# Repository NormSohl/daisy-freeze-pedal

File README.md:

# Daisy Freeze Pedal

A line-level freeze/drone floor pedal (mono in, stereo out) built on the Electrosmith Daisy Seed3, designed for playing hands-free alongside a WARBL wind controller or analog synths. Hold a footswitch to record, release to loop; the loop plays back as a Clouds-style granular freeze with sub-octave, fifth and octave voices.

## Status

Ready to order. The DSP and controls are proven in a browser bench model. The carrier is a bare, all-through-hole board you solder yourself, routed and DRC-clean; the case is a parametric OpenSCAD model. Next: order bare boards and parts, print the case, then port the bench engine to DaisySP.

## Panel

| Control | Type | Function |
|---|---|---|
| Freeze | Soft-touch momentary footswitch | Hold to record (up to 8 s), release to start looping |
| Clear | Soft-touch momentary footswitch | Tap: fade out the oldest layer. Hold 0.7 s: clear all |
| Dry | Pot | Passthrough level |
| Loop | Pot | Frozen 1:1 voice level |
| −8 | Pot | Sub-octave voice (1:2), 28 Hz high-pass |
| +5 | Pot | Fifth voice, 3:2 up or 3:4 down |
| +8 | Pot | Octave voice (2:1) |
| Fade | Pot | Layer swell-in and release time, 20 ms to 8 s |
| Texture | Pot | Macro: grain size, window shape and density, smooth → grainy |
| Single / Multi | Toggle | Single crossfades each capture over the last loop; Multi stacks up to 6 layers |
| +5 up / down | Toggle | Fifth above (3:2) or below (3:4) |
| LED | Bi-color | Red while recording, green while layers play, off when empty |

Fixed in firmware: grain spread, drift (random per-grain detune), output level. No reverb.

## I/O and power

- Three switched 1/4" jacks on the back face: In (mono), Out L/Mono, Out R.
  - The mono input feeds both codec inputs; the voices are spread across the stereo outputs.
  - Nothing in Out R: the firmware sums L+R to Out L (detected through Out R's ring switch).
- Line level in and out, no buffer and no input pad. The Seed3 clips at 3.6 Vpp (+4.3 dBu) and is rated to ±1.8 V, so keep very hot synth outputs turned down.
- The Seed3's own USB-C faces the back wall for 5 V power and firmware updates. Holding Clear at power-up will jump to the bootloader so the case never needs opening to flash.

## Hardware plan

- **One carrier PCB** mounted parallel to the panel carries everything except the footswitches:
  - Top side: seven 9 mm PCB-mount pots (plastic shafts), two PCB-mount mini toggles, LED on a spacer, and six resistors/capacitors.
  - Underside, rear edge: three right-angle 1/4" jacks with threaded bushings (nutted to the back wall so plug forces go into the case) and the Seed3 on female headers, its USB-C facing the back wall.
- **Footswitches** are nutted to the panel and wired to 2-pin locking connectors on the carrier; stomps never load solder joints.
- **Enclosure**: reinforced 3D-printed wedge, PETG or ASA. See [`enclosure/`](enclosure/).

## Parts

| Part | Choice | Notes |
|---|---|---|
| Pots (×7) | Alpha RV09AF-40-20K-B10K: 9 mm, vertical PCB mount, 20 mm knurled plastic shaft, B10K linear ([Jameco 2272207](https://www.jameco.com/z/RV09AF-40-20K-B10K-Taiwan-Alpha-9mm-Linear-Taper-Potentiometer-10K-Ohm-50mW-20-20mm-Long-Vertical-Knurled-Shaft_2272207.html), also Mouser and Tayda; the 25 mm length isn't stocked) | 7.6 mm tall body. Used bare, no knobs or caps: the knurled shaft is the grip, with a painted index line across its top face. |
| Toggles (×2) | E-Switch 100SP1T1B1M2RE (gold contacts; any 100SP1…M2 variant fits the board): SPDT on-on, PCB mount (M2), threaded 1/4"-40 bushing (B1, 8.89 mm) | Catalog p.2: single-pole body 8.89 mm; M2 drawing p.8: pins stand the body 1.5 mm off the board. Bushing base sits 10.39 mm above the PCB and seats on the panel underside; 6.4 mm of thread above the 2.5 mm panel takes the nut. The B4 variant's bushing is unthreaded. |
| Footswitches (×2) | Soft-touch momentary SPST, M12 bushing | Panel-mounted, wired to the carrier. |
| Jacks (×3) | Neutrik NMJ6HCD2: 1/4" stereo, switched, horizontal PCB, chrome ferrule with nut | Axis 7.53 mm from the PCB (drawing: 15.67 body, axis 8.14 below its top), 18.2 mm wide, 11.4 mm panel cut-out, panels under 4.7 mm. Mounted on the carrier underside. |
| Seed sockets | 2× 1×20 female headers, 2.54 mm, 8.5 mm tall | Seed3 hangs below the carrier on its 2.5 mm header spacer, USB-C to the back wall. |
| LED | 5 mm bi-colour red/green, common cathode, 3-lead, on a 4 mm LED spacer | Spacer puts the dome 0.3 mm below the panel top. Driven from two GPIOs through 470 Ω; pick R per die once the LED is chosen (a true-green die needs less). |
| Footswitch pads (×2) | J1/J2, 2 mm JST PH footprint, left unpopulated | Solder 24–26 AWG leads straight into the pads (polarity doesn't matter). A B2B-PH-K header and plug can be fitted later if you want the footswitches unpluggable. |
| Output coupling (×2 each) | 10 µF 25 V X7R radial MLCC (5 mm leads), 100 k ¼ W | One capacitor in series and one resistor to ground per output. |
| LED resistors (×2) | 470 Ω ¼ W | |

The full list is in [`pcb/carrier/fab/bom.csv`](pcb/carrier/fab/bom.csv): 26 parts, all through-hole. Add two 1×20 female headers for the Seed3; the footswitches are wired straight to J1/J2.

Board stack (from the datasheets): the toggle's bushing base sits 10.39 mm above the board, so the carrier hangs 10.39 mm under the 2.5 mm panel. Pot bodies (7.6 mm) sit below the panel and the panel holes bear their shafts. RV09 shaft length L is measured from the PCB, so a 20 mm shaft stands 7.1 mm above the panel. The panel is 2.5 mm (not thicker) to keep that grip; the board height is fixed by the toggles, so only a thinner panel adds shaft.

## Carrier board

KiCad 7 project in [`pcb/carrier/`](pcb/carrier/): schematic, routed two-layer board, Gerbers and a hand-solder parts list. Everything is generated by scripts so the schematic, board and case stay in step. Rev B is all through-hole with only six small parts: two output capacitors, two output bleed resistors and two LED resistors. The pots go straight to the ADC pins (the firmware smooths them), the Seed3's own supply filtering is enough, and the toggles, footswitches and Out R detect use the Seed's internal pull-ups.

| Board side | Parts |
|---|---|
| Top (faces the panel) | 7 pots, 2 toggles, LED, 2 footswitch connectors, 6 resistors/capacitors |
| Bottom | Seed3 on sockets, 3 jacks along the rear edge |

**Seed pin map**

| Function | Seed pin | Notes |
|---|---|---|
| Dry, Loop, −8, +5, +8, Fade, Texture pots | A0–A6 (pins 22–28) | Pot ends on 3V3A / GND; wiper straight to the pin |
| Audio in | 16 and 17 | Mono input wired to both codec inputs. The In jack's tip switch grounds the input when empty. Seed3 limit 3.6 Vpp (+4.3 dBu), absolute max ±1.8 V. |
| Audio out L / R | 18 / 19 | 10 µF in series and 100 k to ground at each jack, as in the Seed3 reference circuit |
| Single / Multi toggle | D7 (pin 8) | Toggle switches the pin between 3V3D and GND |
| +5 up / down toggle | D8 (pin 9) | Same |
| Freeze / Clear footswitches | D9 / D10 (pins 10 / 11) | To GND; use internal pull-ups |
| LED red / green | D11 / D12 (pins 12 / 13) | 470 Ω each |
| Out R plug detect | D26 (pin 33) | Out R's ring is grounded and its ring-normal contact goes to the pin: empty jack reads low, any plug (TS or TRS) reads high. Use the internal pull-up. |
| Power | 3V3A (21), 3V3D (38), AGND (20), DGND (40) | AGND and DGND both tie to one carrier ground (the datasheet requires them joined) |

The Seed3 is powered from its own USB-C. VIN is left unconnected. Use an isolated or battery USB supply if the mains-grounded synth and amp cause hum.

| Top side | Bottom side (seen from below) |
|---|---|
|  |  |

**Regenerate**

```
cd pcb/carrier
python3 gen_schematic.py   # writes carrier.kicad_sch and the project libraries
python3 gen_pcb.py         # reads the netlist and the case geometry, places parts in carrier.kicad_pcb
python3 route_pcb.py freerouting.jar   # design rules, Freerouting autoroute, GND pour both layers + stitching vias, DRC report
python3 make_fab.py        # Gerbers + drill (fab/carrier-gerbers.zip) and the hand-solder bom.csv
```

Routing: 0.3 mm tracks, 0.25 mm clearance, 0.8/0.4 mm vias, ground poured on both layers and stitched together with a via grid. The DRC report (`drc-report.txt`) shows 0 violations and 0 unconnected pads. `route_pcb.py` uses [Freerouting](https://github.com/freerouting/freerouting) 1.9 (Java) and retries until every connection is made.

**Ordering**
- Upload `fab/carrier-gerbers.zip` for a bare 2-layer, 1.6 mm board (152 × 100 mm). No assembly; the cheapest economy shipping is fine.
- Every part is through-hole and hand-soldered; see Board assembly below.

`gen_pcb.py` reads every panel and back-wall position from the OpenSCAD model through `enclosure_params.scad`, so moving a control in the case moves its part on the board. Fitting the Seed's pin rows between the +5 and +8 pots set the top-row spacing to 32 mm; the narrowest gap on the board is 1.2 mm between a pot tab hole and a Seed pin.

**Checked**
- Jack fit: Neutrik rates the NMJ6HCD2 for panels under 4.7 mm, so the 3 mm printed back wall is fine.
- Seed3 (datasheet v2.1) pinout is identical to the original Seed; USB-C overhangs the board end by 1.55 mm, so the back-wall slot is 14 × 9 mm.
- An independent review checked footprints, pin map, wiring and fab files against the datasheets; its fixes are applied.
- Printed holes often come out slightly undersize: if a jack or toggle won't go in, open the hole with an 11.5 mm drill or step bit (jacks) or a 1/4" bit (toggles).
- With a meter, confirm the NMJ6HCD2 ring-normal (RN) contact opens on plug insertion before relying on Out R detection; the drawing has no contact diagram.

## Board assembly

- **Everything by hand:** the board is ordered bare and every part is through-hole.
- **Small parts first:** the six resistors and capacitors lie flat, so solder them before anything tall.
- **Alignment jig (solder last):** fit the pots, toggles and jacks into the board unsoldered, seat the board on its standoffs in the printed shell, and run the toggle and jack nuts on so every part lines up with its hole. Then solder from the underside. Everything ends up square to the panel and back wall.
- **Footswitches** are nutted to the panel and plug into 2-pin locking connectors on the carrier after the board is in.

## Repository layout

```
bench/index.html                 Browser prototype of the pedal (AudioWorklet DSP + simulated synth input)
enclosure/freeze_pedal_case.scad Parametric OpenSCAD enclosure
enclosure/stl/                   shell.stl, plate.stl (first pass, renders manifold)
enclosure/renders/               Front, side and underside views
pcb/carrier/                     KiCad 7 carrier board: schematic, placed board, generator scripts
```

## Bench prototype

Open `bench/index.html` in a browser (Chrome, Safari or Firefox). Power on, start the melody or play the keyboard, then hold Freeze. The DSP engine is written as a plain class so it ports to DaisySP C++ almost line for line:

- 8 s stereo ring buffer, record buffer preallocated (no allocation on the audio thread at capture)
- Grains read with Hermite interpolation; voices above 1:1 read a copy low-passed at 0.2·fs to avoid aliasing
- Up to 6 layers, each with its own fade envelope; 4 voices per layer
- tanh soft clip at the output

## Enclosure

- Wedge, front to back only: 35 mm overall at the front rising to 50 mm at the back (≈5.7° panel), 150 mm deep, 160 mm wide. ≈29 mm of clearance under the panel at the footswitches (the model echoes this value); jacks sit low on the back wall so their bodies pass under the carrier PCB.
- Flat 5 mm removable bottom plate for a full rubber mat. It's held by six M3×8 socket-head screws (four corners, front and back centre) that go up through counterbored holes in the plate into M3 heat-set inserts (Ruthex 4.6 mm) pressed into bosses along the bottom edge of the shell walls. Install the inserts from below with the shell upside down.

- Each footswitch: thickened panel pad plus two 8 × 8 mm columns straight down to the bottom plate, so stomps load the floor rather than the panel.
- Panel face is completely flat (no ridges or recesses) so the shell prints face-down without supports; the back wall, square to the panel, prints vertical. The carrier sits 10.39 mm under the panel (set by the toggles) and the panel holes bear the pot shafts.

- Back wall is perpendicular to the panel so the board-mounted jacks meet it square. Jack and USB openings are slots open at the bottom: the carrier slides up into the shell, then the jack nuts clamp it to the wall.
- `part = "carrier"` renders the board, jacks and Seed as reference geometry for fit checks.
- Print the shell face down (panel face on the bed). 4+ perimeters, 40%+ gyroid, 100% infill around the footswitch pads.

Part dimensions in the SCAD file come from the datasheets (Alpha RV09, E-Switch 100 series, Neutrik NMJ6HCD2, Seed3 v2.1). The footswitch body depth is the one value still to confirm against the switch you buy; there is about 29 mm of clearance.

## License

MIT. See [LICENSE](LICENSE). Covers the firmware model, bench, enclosure design files and documentation in this repository.

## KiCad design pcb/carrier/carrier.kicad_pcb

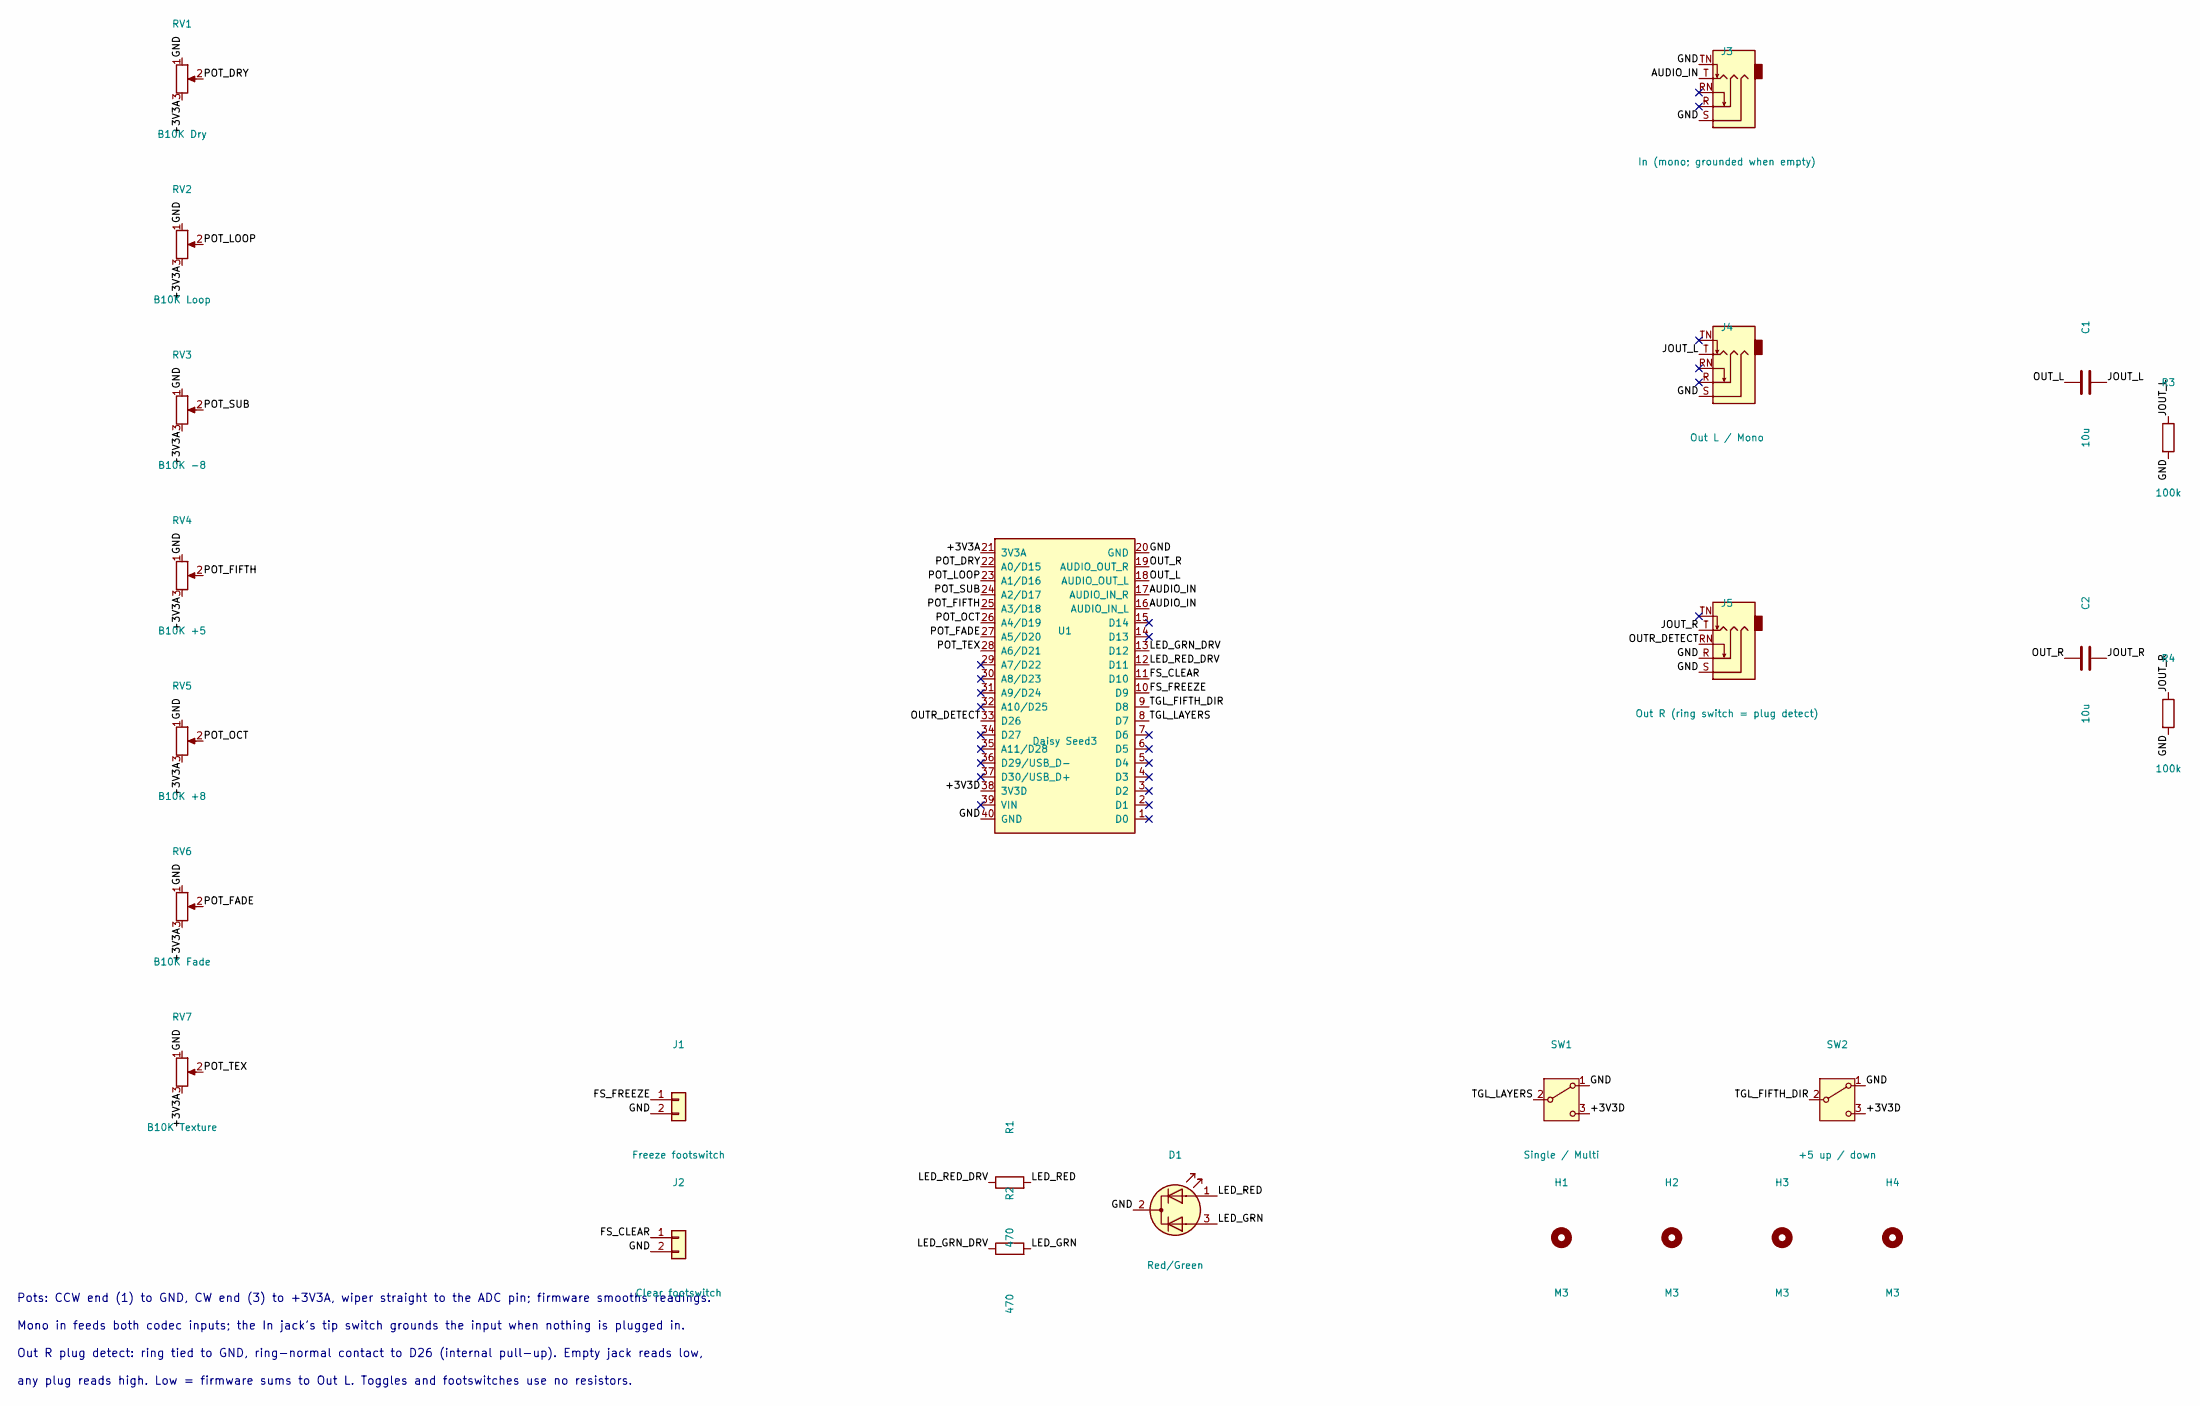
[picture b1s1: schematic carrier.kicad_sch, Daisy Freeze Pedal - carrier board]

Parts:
C1, C2: 10u; C_Disc_D5.0mm_W2.5mm_P5.00mm; MPN 10 uF 25 V X7R radial MLCC, 5.08 mm lea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
D1: Red/Green; LED_D5.0mm-3; MPN 5 mm bi-colour LED, common cathode (red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
H1, H2, H3, H4: M3; MountingHole_3.2mm_M3
J1: Freeze footswitch; JST_PH_B2B-PH-K_1x02_P2.00mm_Vertical; MPN JST B2B-PH-K; footswitch: soft-touch mo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
J2: Clear footswitch; JST_PH_B2B-PH-K_1x02_P2.00mm_Vertical; MPN JST B2B-PH-K; footswitch: soft-touch mo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
J3: In (mono; grounded when empty); Jack_6.35mm_Neutrik_NMJ6HCD2_Horizontal_FabOnlySilk; MPN Neutrik NMJ6HCD2
J4: Out L / Mono; Jack_6.35mm_Neutrik_NMJ6HCD2_Horizontal_FabOnlySilk; MPN Neutrik NMJ6HCD2
J5: Out R (ring switch = plug detect); Jack_6.35mm_Neutrik_NMJ6HCD2_Horizontal_FabOnlySilk; MPN Neutrik NMJ6HCD2
R1, R2: 470; R_Axial_DIN0207_L6.3mm_D2.5mm_P7.62mm_Horizontal; MPN 470R 1/4 W (choose per LED)
R3, R4: 100k; R_Axial_DIN0207_L6.3mm_D2.5mm_P7.62mm_Horizontal; MPN 100k 1/4 W metal film
RV1: B10K Dry; Potentiometer_Alpha_RV09AF-40_Vertical; MPN Alpha RV09AF-40-25K-B10K (25 mm knurled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
RV2: B10K Loop; Potentiometer_Alpha_RV09AF-40_Vertical; MPN Alpha RV09AF-40-25K-B10K (25 mm knurled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
RV3: B10K −8; Potentiometer_Alpha_RV09AF-40_Vertical; MPN Alpha RV09AF-40-25K-B10K (25 mm knurled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
RV4: B10K +5; Potentiometer_Alpha_RV09AF-40_Vertical; MPN Alpha RV09AF-40-25K-B10K (25 mm knurled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
RV5: B10K +8; Potentiometer_Alpha_RV09AF-40_Vertical; MPN Alpha RV09AF-40-25K-B10K (25 mm knurled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
RV6: B10K Fade; Potentiometer_Alpha_RV09AF-40_Vertical; MPN Alpha RV09AF-40-25K-B10K (25 mm knurled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
RV7: B10K Texture; Potentiometer_Alpha_RV09AF-40_Vertical; MPN Alpha RV09AF-40-25K-B10K (25 mm knurled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
SW1: Single / Multi; SW_E-Switch_100SP_M2_PCB; MPN E-Switch 100SP1T1B1M2QE
SW2: +5 up / down; SW_E-Switch_100SP_M2_PCB; MPN E-Switch 100SP1T1B1M2QE
U1: Daisy Seed3; DaisySeed_Socket_2x20; MPN Electrosmith Daisy Seed3 (on 2x 1x20 fe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

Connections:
+3V3A: RV1.3, RV2.3, RV3.3, RV4.3, RV5.3, RV6.3, RV7.3, U1.21 (3V3A)
+3V3D: SW1.3 (C), SW2.3 (C), U1.38 (3V3D)
AUDIO_IN: J3.T, U1.16 (AUDIO_IN_L), U1.17 (AUDIO_IN_R)
FS_CLEAR: J2.1, U1.11 (D10)
FS_FREEZE: J1.1, U1.10 (D9)
GND: D1.2 (K), J1.2, J2.2, J3.S, J3.TN, J4.S, J5.R, J5.S, R3.2, R4.2, RV1.1, RV2.1, RV3.1, RV4.1, RV5.1, RV6.1, RV7.1, SW1.1 (A), SW2.1 (A), U1.20 (GND), U1.40 (GND)
JOUT_L: C1.2, J4.T, R3.1
JOUT_R: C2.2, J5.T, R4.1
LED_GRN: D1.3 (A2), R2.2
LED_GRN_DRV: R2.1, U1.13 (D12)
LED_RED: D1.1 (A1), R1.2
LED_RED_DRV: R1.1, U1.12 (D11)
OUTR_DETECT: J5.RN, U1.33 (D26)
OUT_L: C1.1, U1.18 (AUDIO_OUT_L)
OUT_R: C2.1, U1.19 (AUDIO_OUT_R)
POT_DRY: RV1.2, U1.22 (A0/D15)
POT_FADE: RV6.2, U1.27 (A5/D20)
POT_FIFTH: RV4.2, U1.25 (A3/D18)
POT_LOOP: RV2.2, U1.23 (A1/D16)
POT_OCT: RV5.2, U1.26 (A4/D19)
POT_SUB: RV3.2, U1.24 (A2/D17)
POT_TEX: RV7.2, U1.28 (A6/D21)
TGL_FIFTH_DIR: SW2.2 (B), U1.9 (D8)
TGL_LAYERS: SW1.2 (B), U1.8 (D7)

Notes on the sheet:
Pots: CCW end (1) to GND, CW end (3) to +3V3A, wiper straight to the ADC pin; firmware smooths readings.
Mono in feeds both codec inputs; the In jack's tip switch grounds the input when nothing is plugged in.
Out R plug detect: ring tied to GND, ring-normal contact to D26 (internal pull-up). Empty jack reads low,
any plug reads high. Low = firmware sums to Out L. Toggles and footswitches use no resistors.

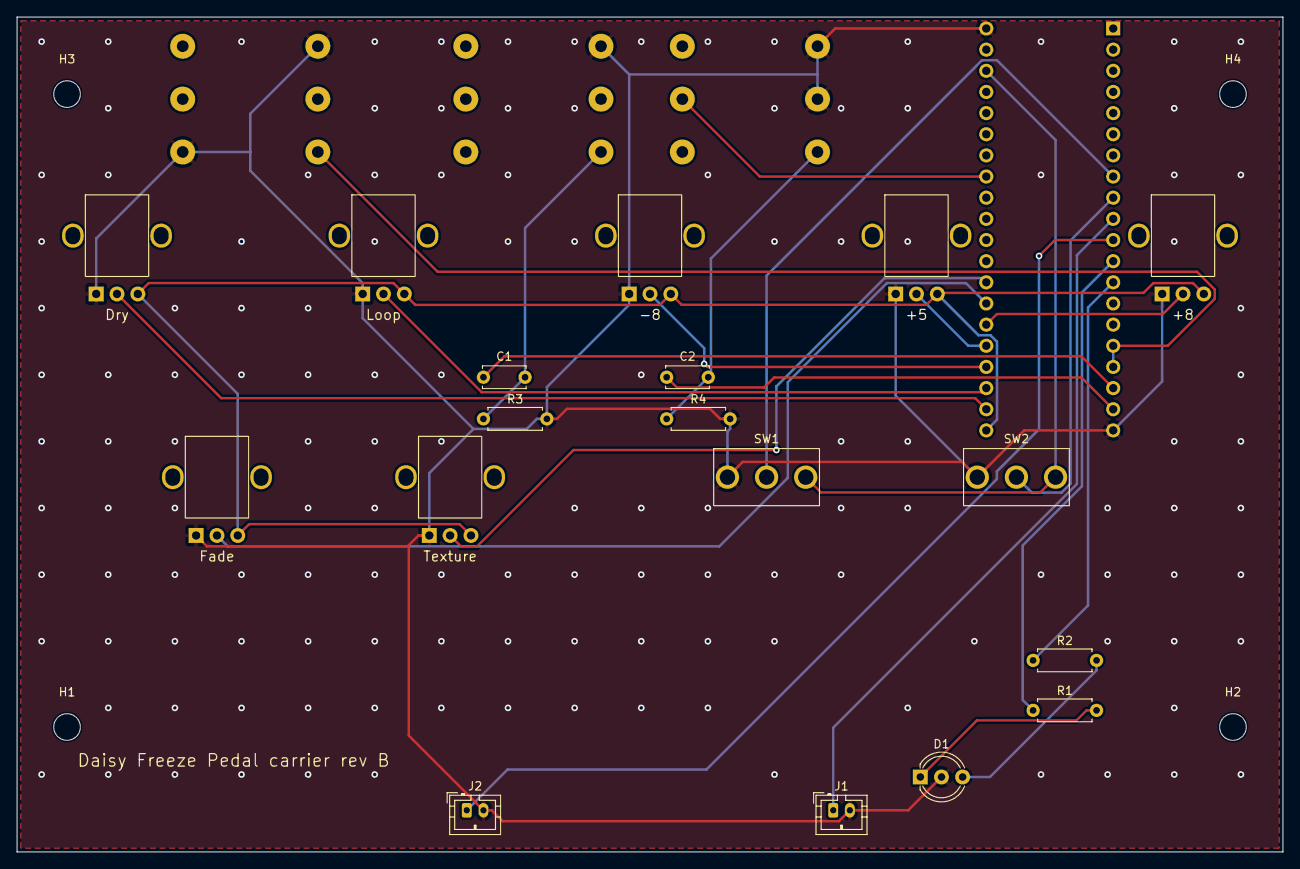
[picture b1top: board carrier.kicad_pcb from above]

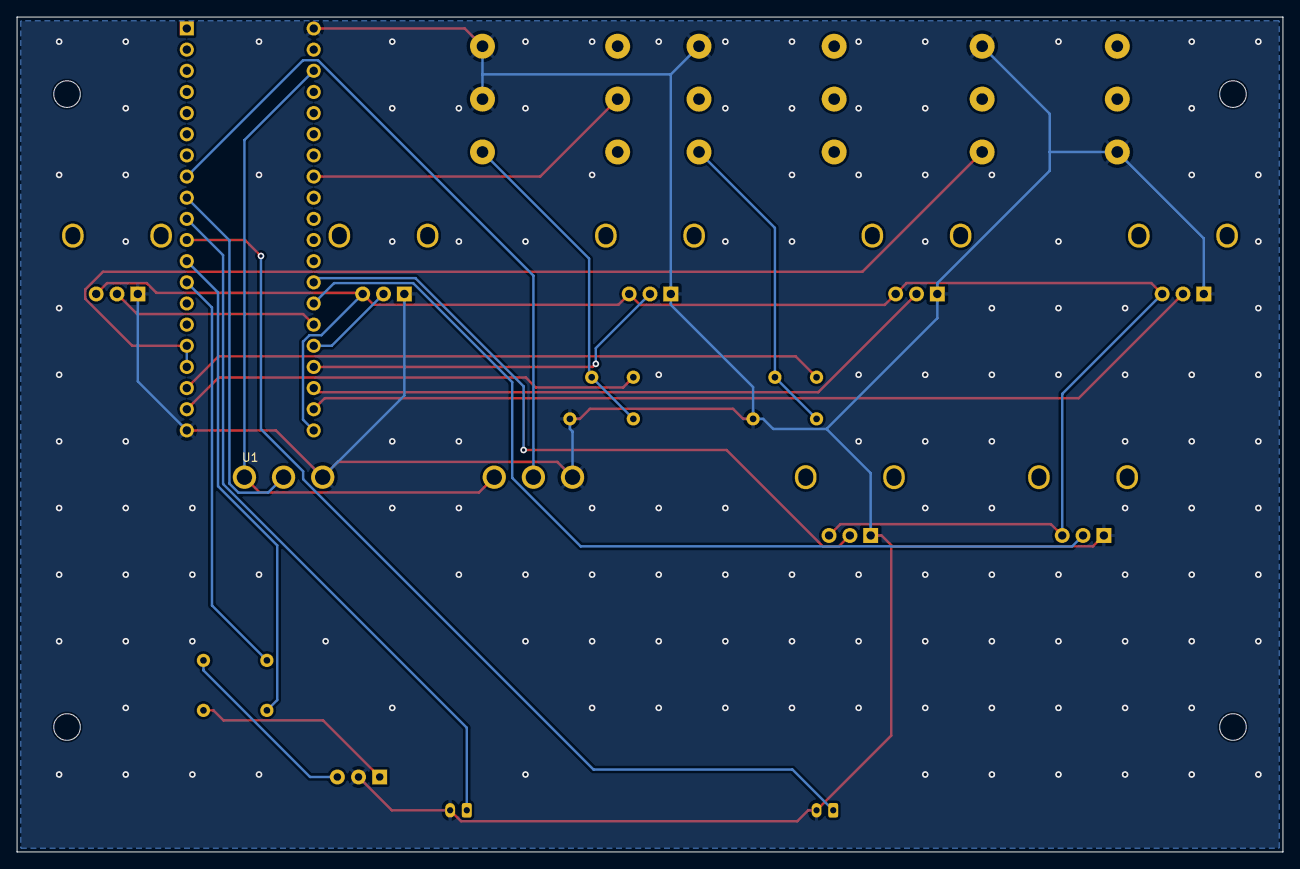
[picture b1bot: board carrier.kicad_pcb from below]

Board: 2 copper layers, 152.0 x 100.2 mm, 26 parts (4 on the bottom side), 24 nets.

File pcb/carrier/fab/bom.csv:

Qty,References,Value,Part
2,C1 C2,10u,"10 uF 25 V X7R radial MLCC, 5.08 mm leads (e.g. TDK FG28X7R1E106KRT06)"
1,D1,Red/Green,"5 mm bi-colour LED, common cathode (red/green), on a 5 mm spacer"
1,J1,Freeze footswitch,"JST B2B-PH-K; footswitch: soft-touch momentary SPST, panel mounted"
1,J2,Clear footswitch,"JST B2B-PH-K; footswitch: soft-touch momentary SPST, panel mounted"
1,J3,In (mono; grounded when empty),Neutrik NMJ6HCD2
1,J4,Out L / Mono,Neutrik NMJ6HCD2
1,J5,Out R (ring switch = plug detect),Neutrik NMJ6HCD2
2,R1 R2,470,470R 1/4 W (choose per LED)
2,R3 R4,100k,100k 1/4 W metal film
1,RV1,B10K Dry,Alpha RV09AF-40-25K-B10K (25 mm knurled shaft)
1,RV2,B10K Loop,Alpha RV09AF-40-25K-B10K (25 mm knurled shaft)
1,RV3,B10K −8,Alpha RV09AF-40-25K-B10K (25 mm knurled shaft)
1,RV4,B10K +5,Alpha RV09AF-40-25K-B10K (25 mm knurled shaft)
1,RV5,B10K +8,Alpha RV09AF-40-25K-B10K (25 mm knurled shaft)
1,RV6,B10K Fade,Alpha RV09AF-40-25K-B10K (25 mm knurled shaft)
1,RV7,B10K Texture,Alpha RV09AF-40-25K-B10K (25 mm knurled shaft)
1,SW1,Single / Multi,E-Switch 100SP1T1B1M2QE
1,SW2,+5 up / down,E-Switch 100SP1T1B1M2QE
1,U1,Daisy Seed3,Electrosmith Daisy Seed3 (on 2x 1x20 female headers)

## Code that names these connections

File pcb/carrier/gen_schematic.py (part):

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         MPN="Neutrik NMJ6HCD2")

# Output coupling (Seed3 reference circuit puts 10u in series at each output); 100k bleeds DC so plugging in doesn't pop
part("C1", "Device:C", "10u", C_TH, (395, 95), {"1": "OUT_L", "2": "JOUT_L"}, rot=90,
     MPN="10 uF ≥25 V X7R radial MLCC, 5.08 mm leads (e.g. TDK FG20X7R1H106KRT06, 50 V, on Digi-Key)")
part("R3", "Device:R", "100k", R_TH, (410, 105), {"1": "JOUT_L", "2": "GND"}, MPN="100k 1/4 W metal film")
part("C2", "Device:C", "10u", C_TH, (395, 145), {"1": "OUT_R", "2": "JOUT_R"}, rot=90,
     MPN="10 uF ≥25 V X7R radial MLCC, 5.08 mm leads (e.g. TDK FG20X7R1H106KRT06, 50 V, on Digi-Key)")
part("R4", "Device:R", "100k", R_TH, (410, 155), {"1": "JOUT_R", "2": "GND"}, MPN="100k 1/4 W metal film")

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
